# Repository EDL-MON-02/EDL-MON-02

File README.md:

# Robotic Vacuum Cleaner Project

Welcome to the repository for our Robotic Vacuum Cleaner project! Our goal is to develop an autonomous vacuum cleaner using Raspberry Pi and ultrasonic sensors for efficient mapping and obstacle avoidance.

## Overview

The robotic vacuum cleaner we're building is engineered to seamlessly navigate through rooms, detect obstacles, and autonomously clean floors. It's powered by a Raspberry Pi acting as the central control unit, supported by ultrasonic sensors for precise environment perception. In addition to these core functionalities, our cleaner boasts the following features:

1. **User-friendly App Interface:** Seamlessly switch the robot on/off through our intuitive app, connected via WiFi for effortless control.
   
2. **Scheduled Cleaning:** Take advantage of our scheduling feature to automate cleaning sessions according to your preferences, eliminating the need for manual intervention.
   
3. **Wet Mopping Capability:** Beyond traditional dry vacuuming, our cleaner offers a wet mopping mode, utilizing an integrated water tank and mop pad for thorough floor cleaning.

## Repository Structure

- **CAD Files:** This directory houses all CAD (Computer-Aided Design) files for the mechanical components, including the chassis, wheels, and structural elements.
  
- **PCB Files:** Here, you'll find the PCB (Printed Circuit Board) design files for the electronic components, such as motor drivers, sensor interfaces, and power distribution modules.
  
- **Circuit Design:** Dive into detailed schematics and diagrams outlining the electrical connections and component layout for a comprehensive understanding of the vacuum cleaner's circuitry.
  
- **Raspberry Pi Code(code):** Explore the source code tailored for the Raspberry Pi, responsible for high-level control, decision-making, and seamless communication with sensors and actuators.

- **Web Server + Flutter App:** Explore the code for the flask server and flutter app by installing flutter and flask locally on your local network.
- **Simulation Code:** Access simulation code used to rigorously test and validate the performance of our robotic vacuum cleaner in virtual environments.

## How to Use

1. **CAD Files:** Utilize compatible CAD software (e.g., SolidWorks, AutoCAD) to view and modify the mechanical design of the vacuum cleaner components.
  
2. **PCB Files:** Open the PCB design files using Electronic Design Automation (EDA) software (e.g., KiCad, Altium Designer) to visualize and refine the electronic layout.
  
3. **Circuit Design:** Review comprehensive schematics and diagrams to gain insights into electrical connections and component placement within the vacuum cleaner.
  
4. **Raspberry Pi Code:** Clone or download the repository, then refer to the README.md file within the Raspberry Pi Code directory for instructions on setting up the software environment and deploying it on your Raspberry Pi.
  
5. **Simulation Code:** Clone or download the repository, then follow the instructions in the README.md file within the Simulation Code directory to configure and run simulations of the robotic vacuum cleaner.

## Team members

- Pratik Yabaji (210070094)
- Sumit Londhe (210070089)
- Arya Agarwal (210070012)
- Alok Kumar (210070006)

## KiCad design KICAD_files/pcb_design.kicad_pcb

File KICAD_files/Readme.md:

# Robotic Vacuum Cleaner PCB Design

Welcome to the KiCad PCB design files repository for our Robotic Vacuum Cleaner project! This repository contains all the necessary files for designing the printed circuit board (PCB) used in our robotic vacuum cleaner.

## Overview

The PCB plays a crucial role in the functionality of our robotic vacuum cleaner, as it serves as the central hub for controlling various electronic components, including motor drivers, sensor interfaces, and power distribution modules.

## Repository Structure

- **KiCad Files:** This directory contains both the schematics and layout files for the PCB design. The files are organized to facilitate easy access and modification of the design.

- **Gerber Files:** This directory contains the Gerber files generated from the PCB layout, which are used for manufacturing the actual PCB.

## How to Use

1. **KiCad Files:** Open the KiCad project files (.pro) using KiCad EDA (Electronic Design Automation) software. Inside the project, you will find both the schematic and layout files, allowing you to review and modify the design as needed.

2. **Gerber Files:** These files are ready for manufacturing. You can use them to order the fabrication of the PCB from a PCB manufacturer.

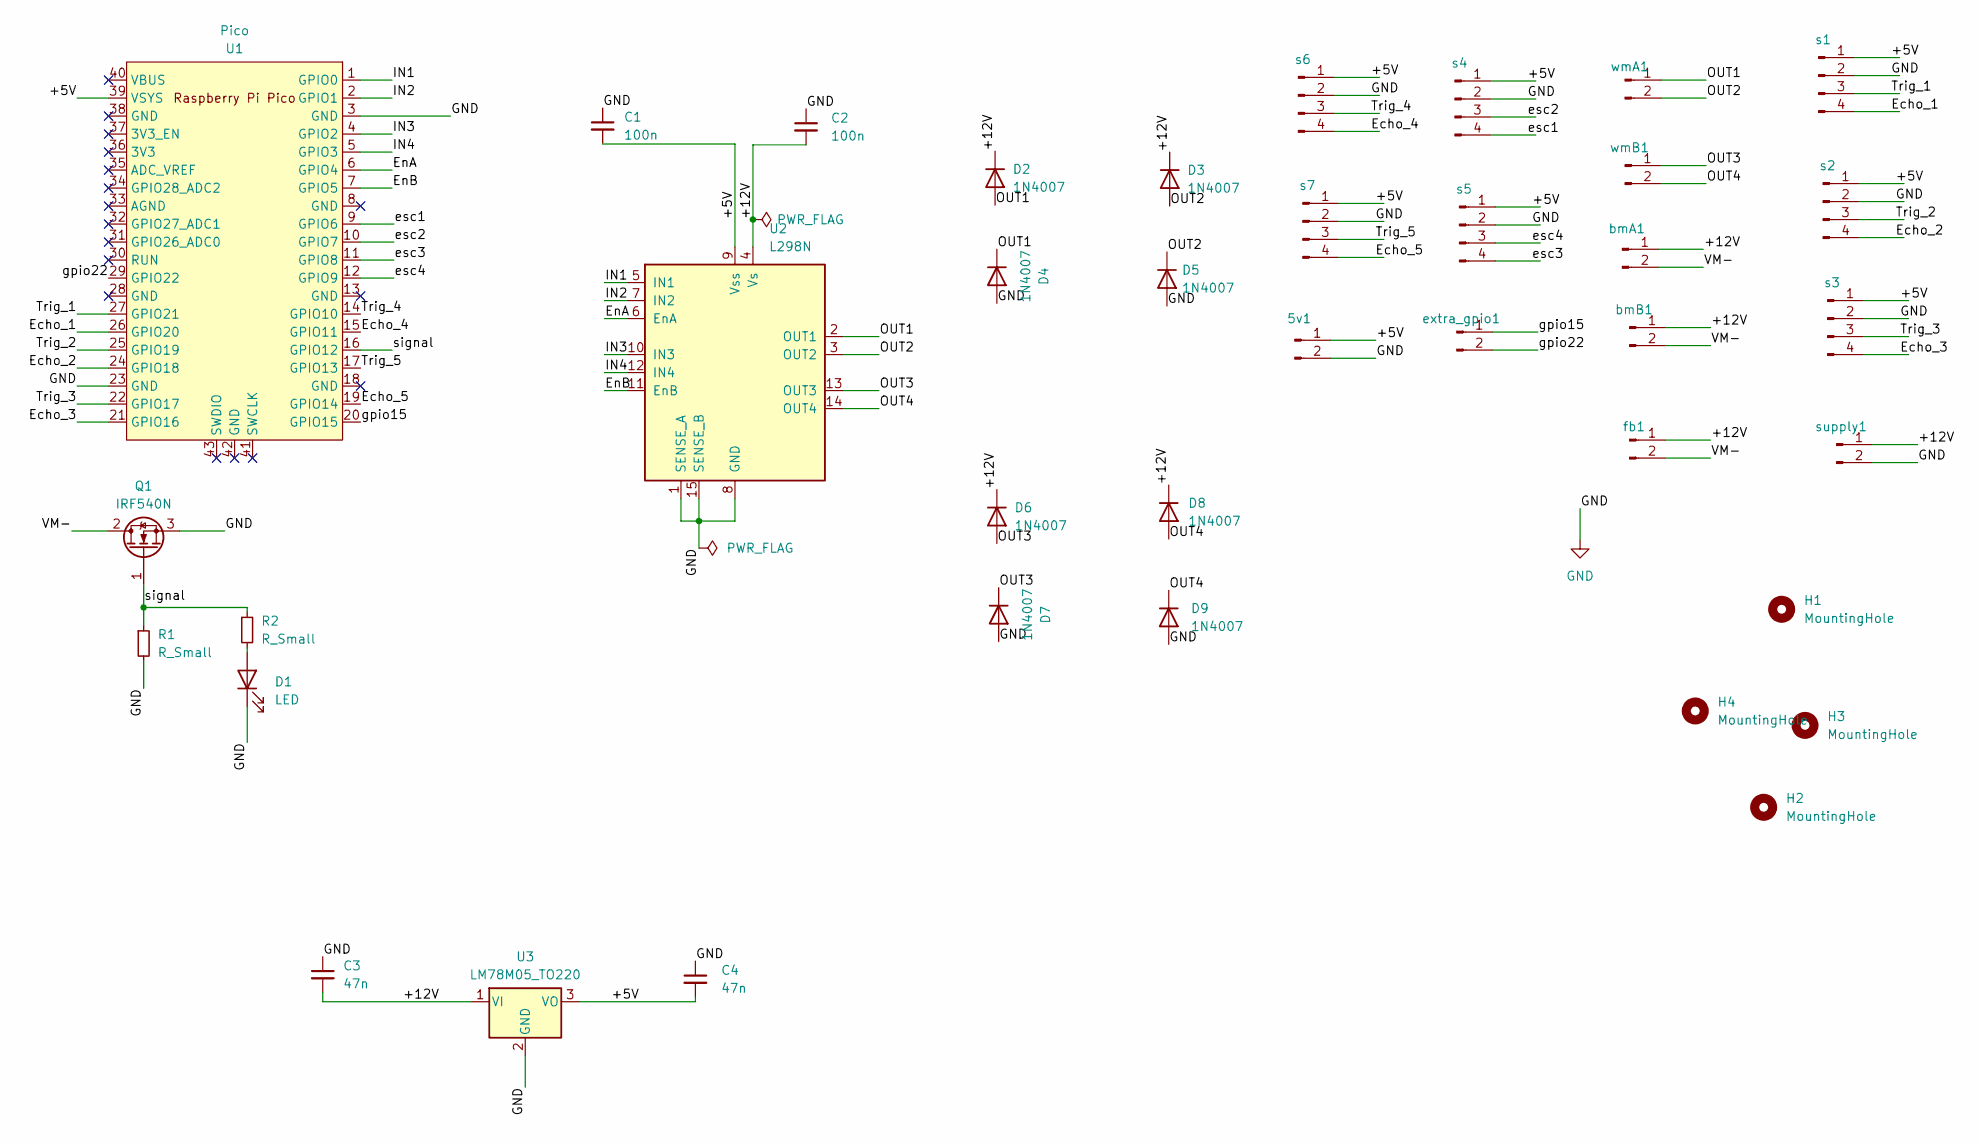
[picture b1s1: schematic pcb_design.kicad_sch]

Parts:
5v1: TerminalBlock_Phoenix_MKDS-1,5-2-5.08_1x02_P5.08mm_Horizont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
C1, C2: 100n; C_Disc_D5.0mm_W2.5mm_P5.00mm
C3, C4: 47n; C_Disc_D5.0mm_W2.5mm_P5.00mm
D1: LED; LED_1206_3216Metric
D2, D3, D4, D5, D6, D7, D8, D9: 1N4007; D_DO-41_SOD81_P10.16mm_Horizontal
H1, H2, H3, H4: MountingHole; MountingHole_3mm
Q1: IRF540N; TO-220-3_Vertical
R1, R2: R_Small; R_Axial_DIN0309_L9.0mm_D3.2mm_P12.70mm_Horizontal
U1: Pico; RPi_Pico_SMD_TH
U2: L298N; TO-220-15_P2.54x2.54mm_StaggerOdd_Lead4.58mm_Vertical
U3: LM78M05_TO220; TO-220-3_Vertical
bmA1: TerminalBlock_Phoenix_MKDS-1,5-2-5.08_1x02_P5.08mm_Horizont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
bmB1: TerminalBlock_Phoenix_MKDS-1,5-2-5.08_1x02_P5.08mm_Horizont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
extra_gpio1: PinHeader_1x02_P2.54mm_Horizontal
fb1: TerminalBlock_Phoenix_MKDS-1,5-2-5.08_1x02_P5.08mm_Horizont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
s1, s2, s3, s4, s5, s6, s7: PinHeader_1x04_P2.54mm_Horizontal
supply1: TerminalBlock_Phoenix_MKDS-1,5-2-5.08_1x02_P5.08mm_Horizont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
wmA1: TerminalBlock_Phoenix_MKDS-1,5-2-5.08_1x02_P5.08mm_Horizont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
wmB1: TerminalBlock_Phoenix_MKDS-1,5-2-5.08_1x02_P5.08mm_Horizont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

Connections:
/+5V: 5v1.1, C1.2, C4.2, U1.39 (VSYS), U2.9 (Vss), U3.3 (VO), s1.1, s2.1, s3.1, s4.1, s5.1, s6.1, s7.1
/+12V: C2.2, C3.2, D2.1 (K), D3.1 (K), D6.1 (K), D8.1 (K), U2.4 (Vs), U3.1 (VI), bmA1.1, bmB1.1, fb1.1, supply1.1
/Echo_1: U1.26 (GPIO20), s1.4
/Echo_2: U1.24 (GPIO18), s2.4
/Echo_3: U1.21 (GPIO16), s3.4
/Echo_4: U1.15 (GPIO11), s6.4
/Echo_5: U1.19 (GPIO14), s7.4
/EnA: U1.6 (GPIO4), U2.6 (EnA)
/EnB: U1.7 (GPIO5), U2.11 (EnB)
/IN1: U1.1 (GPIO0), U2.5 (IN1)
/IN2: U1.2 (GPIO1), U2.7 (IN2)
/IN3: U1.4 (GPIO2), U2.10 (IN3)
/IN4: U1.5 (GPIO3), U2.12 (IN4)
/OUT1: D2.2 (A), D4.1 (K), U2.2 (OUT1), wmA1.1
/OUT2: D3.2 (A), D5.1 (K), U2.3 (OUT2), wmA1.2
/OUT3: D6.2 (A), D7.1 (K), U2.13 (OUT3), wmB1.1
/OUT4: D8.2 (A), D9.1 (K), U2.14 (OUT4), wmB1.2
/Trig_1: U1.27 (GPIO21), s1.3
/Trig_2: U1.25 (GPIO19), s2.3
/Trig_3: U1.22 (GPIO17), s3.3
/Trig_4: U1.14 (GPIO10), s6.3
/Trig_5: U1.17 (GPIO13), s7.3
/VM-: Q1.2 (D), bmA1.2, bmB1.2, fb1.2
/esc1: U1.9 (GPIO6), s4.4
/esc2: U1.10 (GPIO7), s4.3
/esc3: U1.11 (GPIO8), s5.4
/esc4: U1.12 (GPIO9), s5.3
/gpio15: U1.20 (GPIO15), extra_gpio1.1
/gpio22: U1.29 (GPIO22), extra_gpio1.2
/signal: Q1.1 (G), R1.1, R2.1, U1.16 (GPIO12)
GND: 5v1.2, C1.1, C2.1, C3.1, C4.1, D1.1 (K), D4.2 (A), D5.2 (A), D7.2 (A), D9.2 (A), Q1.3 (S), R1.2, U1.3 (GND), U1.23 (GND), U2.1 (SENSE_A), U2.8 (GND), U2.15 (SENSE_B), U3.2 (GND), s1.2, s2.2, s3.2, s4.2, s5.2, s6.2, s7.2, supply1.2
unnamed: D1.2 (A), R2.2

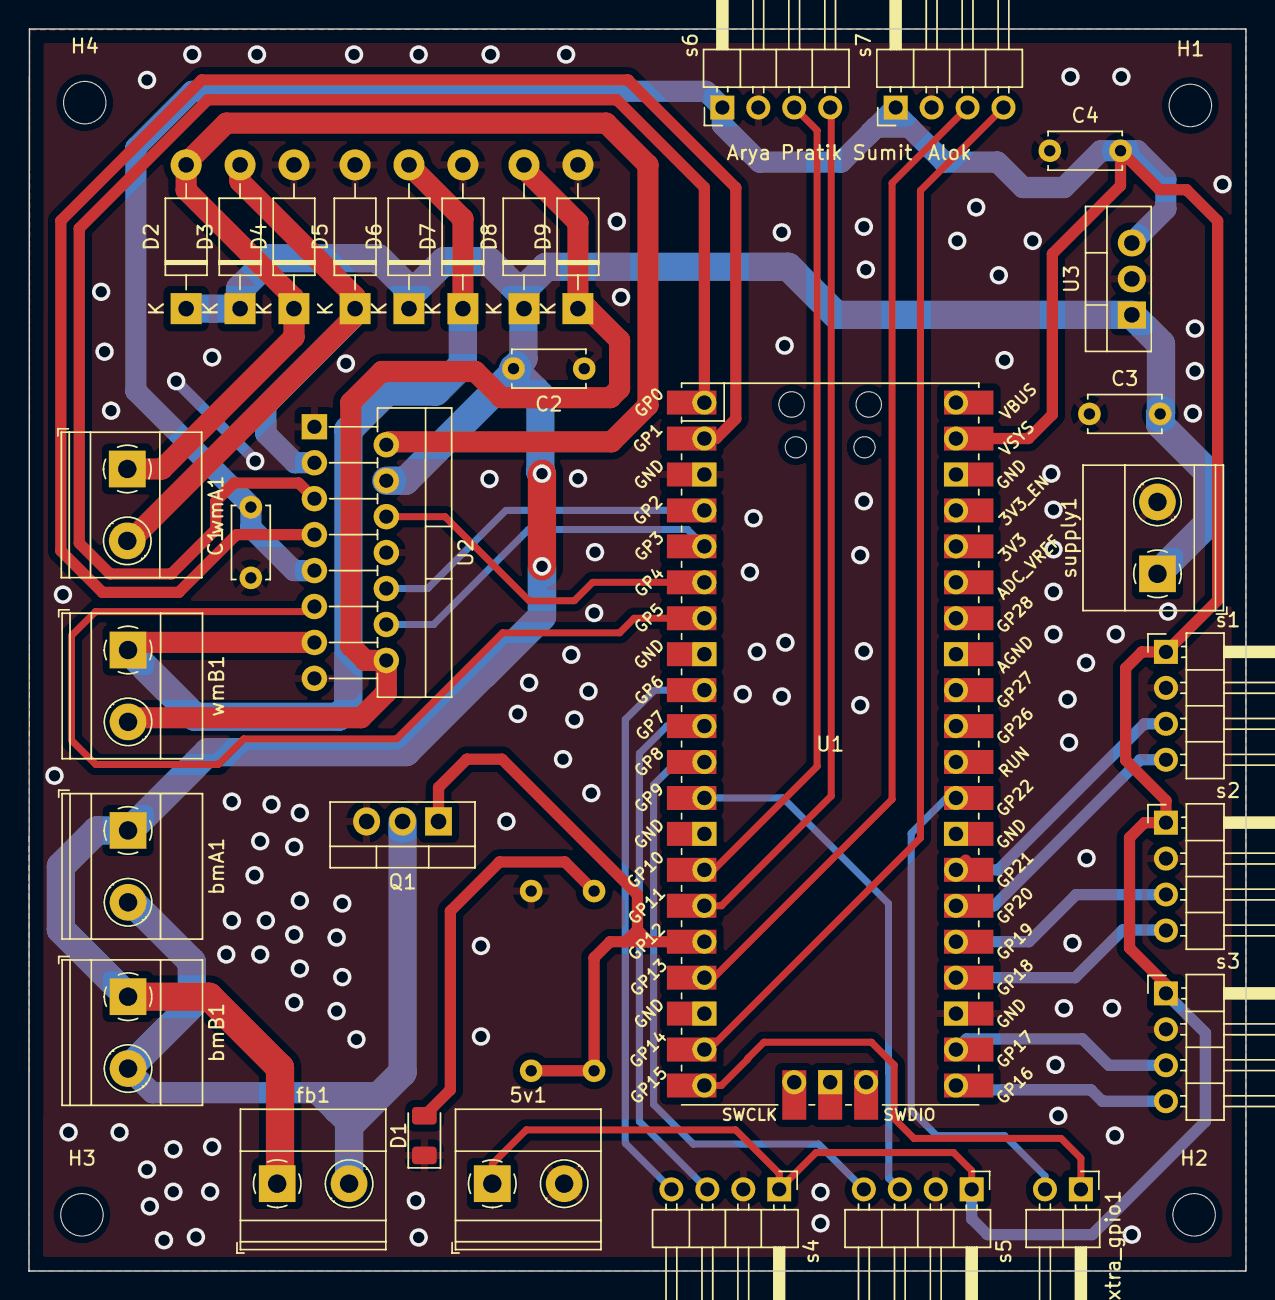
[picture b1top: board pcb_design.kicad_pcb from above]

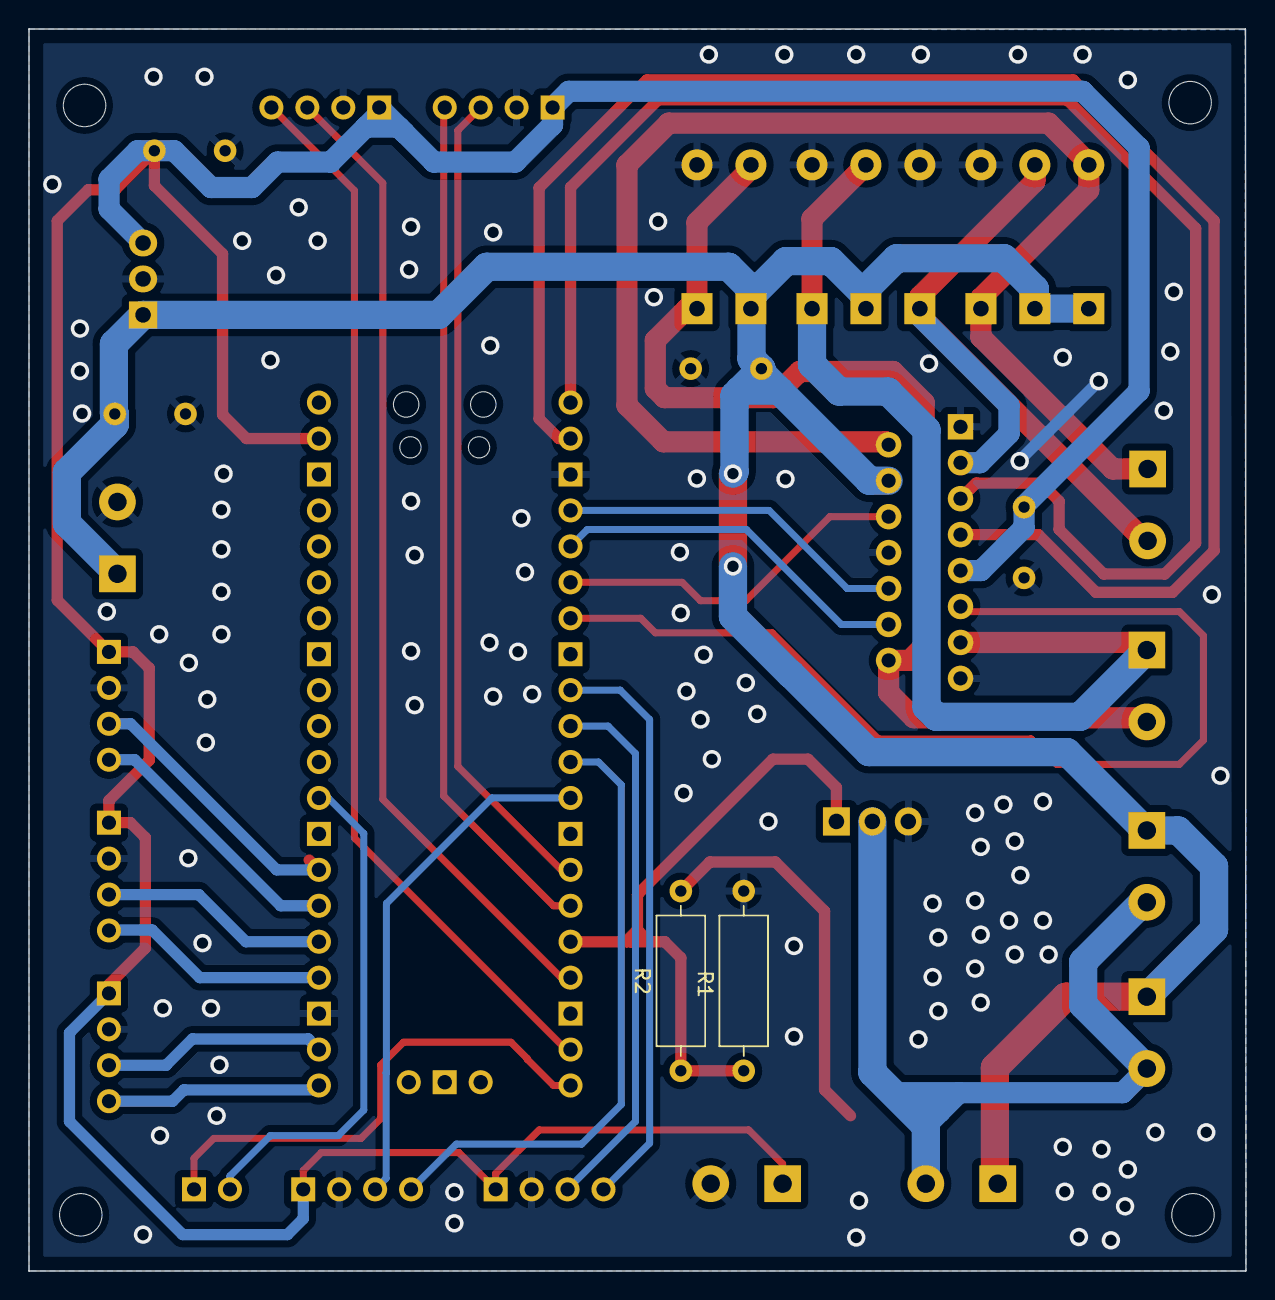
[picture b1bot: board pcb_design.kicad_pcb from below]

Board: 2 copper layers, 86.0 x 87.8 mm, 38 parts (2 on the bottom side), 32 nets.

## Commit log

2024-04-15 Create try
2024-04-15 KICAD files uploaded for PCB
2024-04-19 Pico W code
2024-04-19 server+app code
2024-04-19 add cad files for blower unit and body
2024-04-19 Create Milestone_files
    Contains slides, videos of all milestones.
2024-04-19 Add files via upload
    Milestone slides
2024-04-19 Update README.md with server+app details
